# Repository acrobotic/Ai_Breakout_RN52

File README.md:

## Ai\_Breakout\_RN52

PCB design files (EAGLE) for a breakout board carrying the RN52 Bluetooth Audio
Module.

## Description

Visit our online shop at:

   * https://acrobotic.com/

Designed by ACROBOTIC Industries.  Please consider buying products from us to 
help fund future Open-Source projects like this! We’ll always put our best 
effort in every project, and release all our design files and code for you to 
use. 

## License

Released under the Creative Commons Attribution, Share-Alike license. Please 
check LICENSE.txt for more information. All text above must be included in any 
redistribution.

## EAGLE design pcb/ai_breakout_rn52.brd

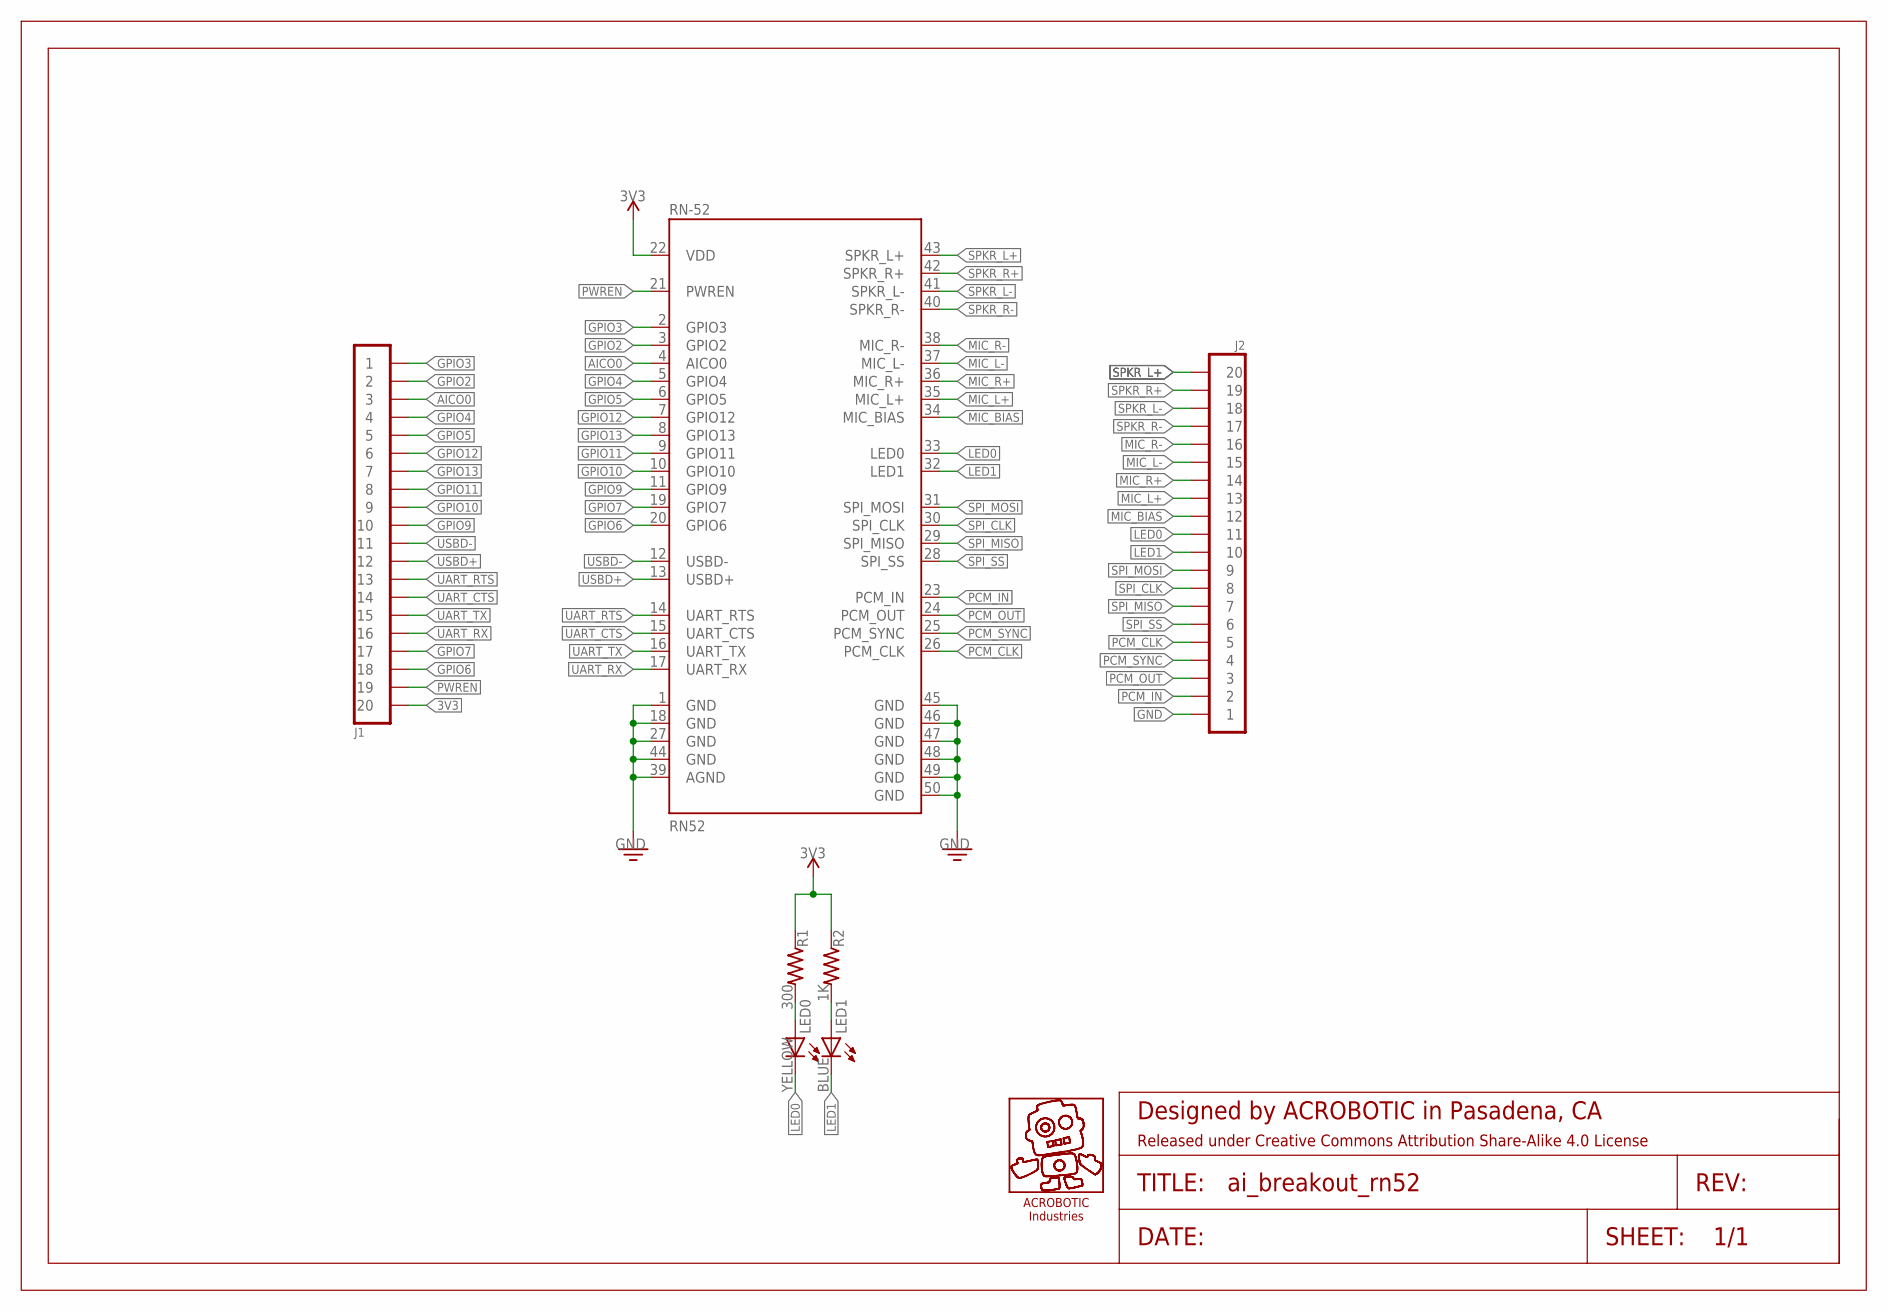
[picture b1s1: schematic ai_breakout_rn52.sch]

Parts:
FRAME1: FRAME-LETTER; CREATIVE-COMMONS
J1, J2: 1X20
LED0: YELLOW; LED-0603
LED1: BLUE; LED-0603
R1: 300; RES-0603
R2: 1K; RES-0603
RN-52: RN52
U$3: AI-LOGOXS; AI-LOGO-XS

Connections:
3V3: J1.20, R1.1, R2.1, RN-52.22 (VDD)
AICO0: J1.3, RN-52.4 (AICO0)
GND: J2.1, RN-52.1 (GND), RN-52.18 (GND), RN-52.27 (GND), RN-52.39 (AGND), RN-52.44 (GND), RN-52.45 (GND), RN-52.46 (GND), RN-52.47 (GND), RN-52.48 (GND), RN-52.49 (GND), RN-52.50 (GND)
GPIO2: J1.2, RN-52.3 (GPIO2)
GPIO3: J1.1, RN-52.2 (GPIO3)
GPIO4: J1.4, RN-52.5 (GPIO4)
GPIO5: J1.5, RN-52.6 (GPIO5)
GPIO6: J1.18, RN-52.20 (GPIO6)
GPIO7: J1.17, RN-52.19 (GPIO7)
GPIO9: J1.10, RN-52.11 (GPIO9)
GPIO10: J1.9, RN-52.10 (GPIO10)
GPIO11: J1.8, RN-52.9 (GPIO11)
GPIO12: J1.6, RN-52.7 (GPIO12)
GPIO13: J1.7, RN-52.8 (GPIO13)
LED0: J2.11, LED0.C, RN-52.33 (LED0)
LED1: J2.10, LED1.C, RN-52.32 (LED1)
MIC_BIAS: J2.12, RN-52.34 (MIC_BIAS)
MIC_L+: J2.13, RN-52.35 (MIC_L+)
MIC_L-: J2.15, RN-52.37 (MIC_L-)
MIC_R+: J2.14, RN-52.36 (MIC_R+)
MIC_R-: J2.16, RN-52.38 (MIC_R-)
unnamed: LED0.A, R1.2
unnamed: LED1.A, R2.2
PCM_CLK: J2.5, RN-52.26 (PCM_CLK)
PCM_IN: J2.2, RN-52.23 (PCM_IN)
PCM_OUT: J2.3, RN-52.24 (PCM_OUT)
PCM_SYNC: J2.4, RN-52.25 (PCM_SYNC)
PWREN: J1.19, RN-52.21 (PWREN)
SPI_CLK: J2.8, RN-52.30 (SPI_CLK)
SPI_MISO: J2.7, RN-52.29 (SPI_MISO)
SPI_MOSI: J2.9, RN-52.31 (SPI_MOSI)
SPI_SS: J2.6, RN-52.28 (SPI_SS)
SPKR_L+: J2.20, RN-52.43 (SPKR_L+)
SPKR_L-: J2.18, RN-52.41 (SPKR_L-)
SPKR_R+: J2.19, RN-52.42 (SPKR_R+)
SPKR_R-: J2.17, RN-52.40 (SPKR_R-)
UART_CTS: J1.14, RN-52.15 (UART_CTS)
UART_RTS: J1.13, RN-52.14 (UART_RTS)
UART_RX: J1.16, RN-52.17 (UART_RX)
UART_TX: J1.15, RN-52.16 (UART_TX)
USBD+: J1.12, RN-52.13 (USBD+)
USBD-: J1.11, RN-52.12 (USBD-)

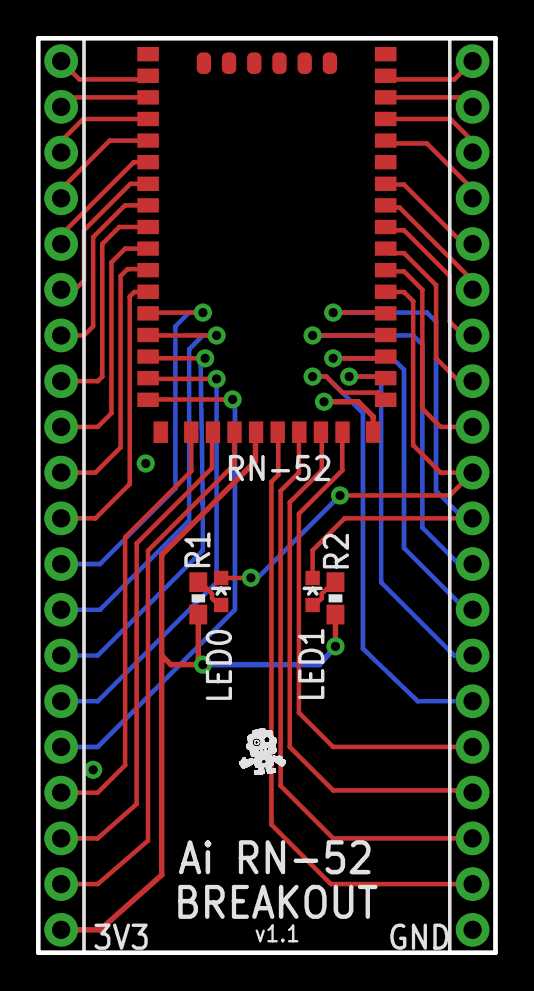
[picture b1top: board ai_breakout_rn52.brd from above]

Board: 2 copper layers, 25.4 x 50.8 mm, 9 parts (0 on the bottom side), 42 nets.

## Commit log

2013-09-22 adding gerbers.
2013-10-11 added BOM
2013-10-11 updating README
2013-10-11 First commit to pages branch
2013-10-11 Comming correct index.html file
2013-10-11 Fixed small typo on README
2013-10-25 New breaboardable version.
2013-10-25 updating schematic pdf.
2013-11-22 minor typo on BOM
2016-04-29 updating

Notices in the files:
parts and their libraries:
Ai_Miscellany: Attribution Share-Alike 4.0 License
Ai_Miscellany: https://creativecommons.org/licenses/by-sa/4.0
Ai_Miscellany: Released under Creative Commons Attribution Share-Alike 4.0 License
